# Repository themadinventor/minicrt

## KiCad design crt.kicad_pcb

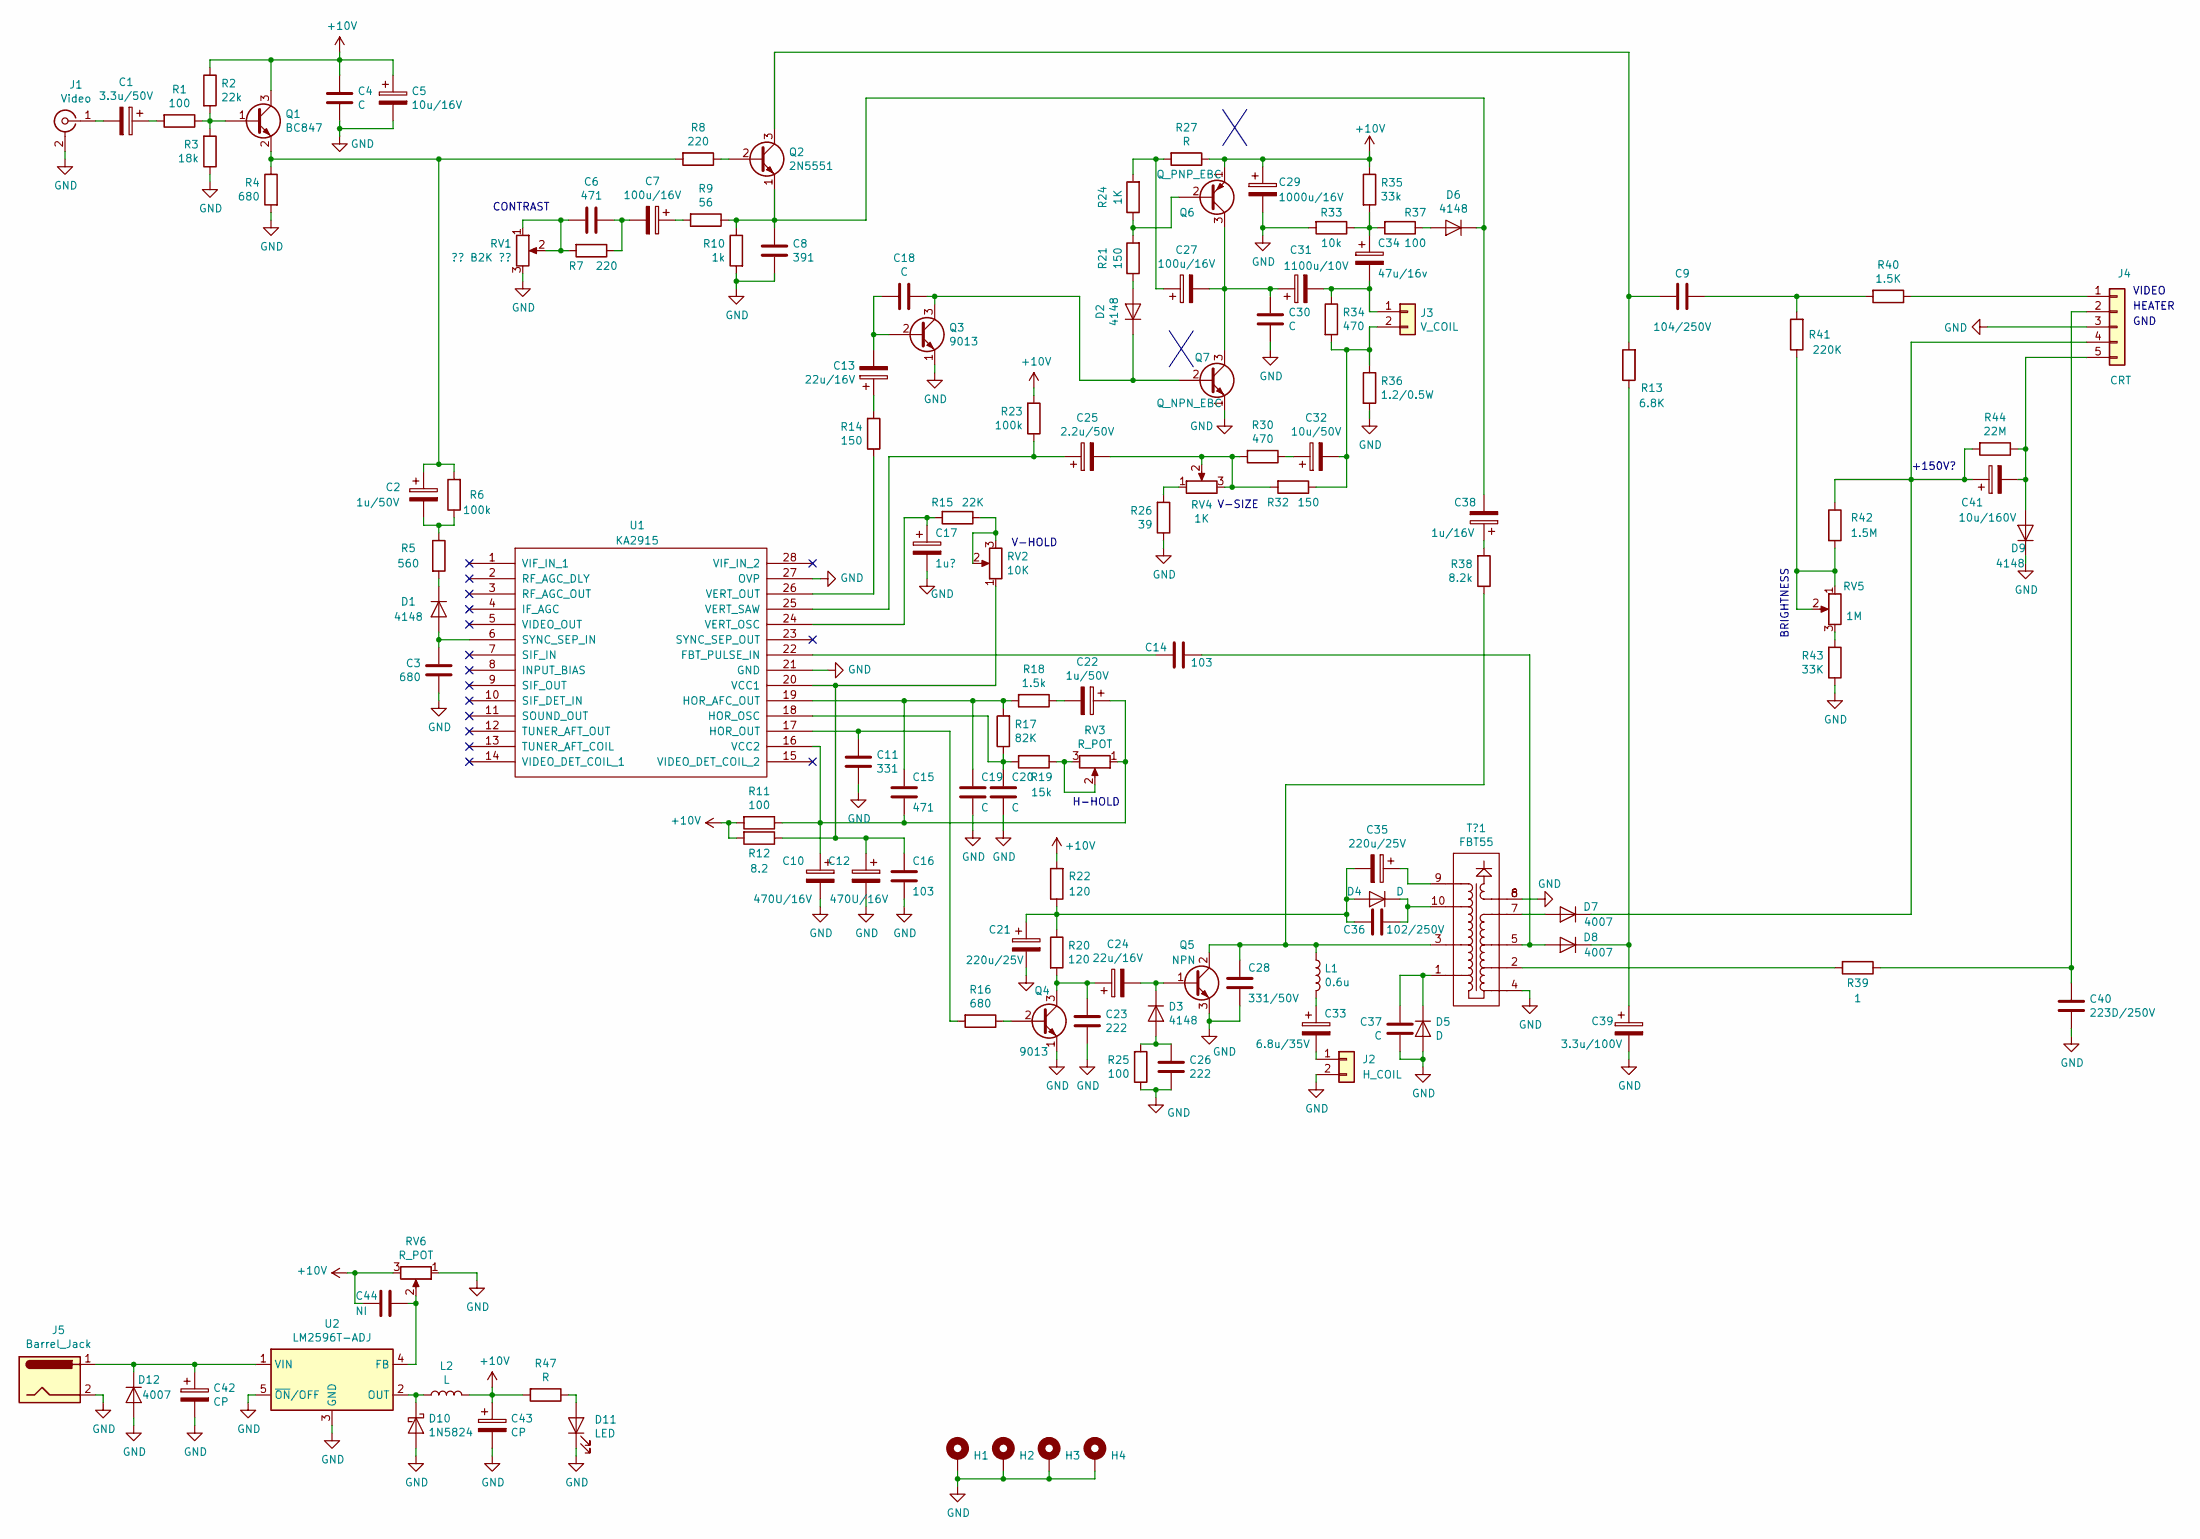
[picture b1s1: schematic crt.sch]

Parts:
C1: 3.3u/50V; CP_Radial_D5.0mm_P2.50mm
C2, C22: 1u/50V; CP_Radial_D5.0mm_P2.50mm
C3: 680; C_Disc_D5.0mm_W2.5mm_P2.50mm
C4, C18, C19, C20, C30, C37: C; C_Disc_D5.0mm_W2.5mm_P2.50mm
C5: 10u/16V; CP_Radial_D5.0mm_P2.50mm
C6, C15: 471; C_Disc_D5.0mm_W2.5mm_P2.50mm
C7: 100u/16V; CP_Radial_D6.3mm_P2.50mm
C8: 391; C_Disc_D5.0mm_W2.5mm_P2.50mm
C9: 104/250V; C_Disc_D7.5mm_W4.4mm_P5.00mm
C10, C12: 470U/16V; CP_Radial_D5.0mm_P2.50mm
C11: 331; C_Disc_D5.0mm_W2.5mm_P2.50mm
C13, C24: 22u/16V; CP_Radial_D5.0mm_P2.50mm
C14, C16: 103; C_Disc_D5.0mm_W2.5mm_P2.50mm
C17: 1u?; CP_Radial_D5.0mm_P2.50mm
C21: 220u/25V; CP_Radial_D8.0mm_P3.50mm
C23, C26: 222; C_Disc_D5.0mm_W2.5mm_P2.50mm
C25: 2.2u/50V; CP_Radial_D5.0mm_P2.50mm
C27: 100u/16V; CP_Radial_D5.0mm_P2.50mm
C28: 331/50V; C_Disc_D5.0mm_W2.5mm_P2.50mm
C29: 1000u/16V; CP_Radial_D7.5mm_P2.50mm
C31: 1100u/10V; CP_Radial_D7.5mm_P2.50mm
C32: 10u/50V; CP_Radial_D7.5mm_P2.50mm
C33: 6.8u/35V; CP_Radial_D10.0mm_P2.50mm
C34: 47u/16v; CP_Radial_D5.0mm_P2.50mm
C35: 220u/25V; CP_Radial_D10.0mm_P2.50mm
C36: 102/250V; C_Disc_D5.0mm_W2.5mm_P2.50mm
C38: 1u/16V; CP_Radial_D5.0mm_P2.50mm
C39: 3.3u/100V; CP_Radial_D5.0mm_P2.50mm
C40: 223D/250V; C_Disc_D7.5mm_W4.4mm_P5.00mm
C41: 10u/160V; CP_Radial_D8.0mm_P3.80mm
C42: CP; CP_Radial_D7.5mm_P2.50mm
C43: CP; CP_Radial_D10.0mm_P2.50mm
C44: NI; C_Disc_D5.0mm_W2.5mm_P2.50mm
D1, D2, D3, D6, D9: 4148; D_DO-35_SOD27_P2.54mm_Vertical_AnodeUp
D4, D5: D; D_DO-41_SOD81_P3.81mm_Vertical_AnodeUp
D7, D8, D12: 4007; D_DO-41_SOD81_P2.54mm_Vertical_AnodeUp
D10: 1N5824; D_DO-41_SOD81_P2.54mm_Vertical_AnodeUp
D11: LED; LED_D3.0mm
H1, H2, H3, H4: MountingHole_Pad; MountingHole_3.2mm_M3_Pad_Via
J1: Video; CUI_RCJ-01
J2: H_COIL; PinHeader_1x02_P2.54mm_Vertical
J3: V_COIL; PinHeader_1x02_P2.54mm_Vertical
J4: CRT; PinHeader_1x05_P2.54mm_Vertical
J5: Barrel_Jack; BarrelJack_CUI_PJ-102AH_Horizontal
L1: 0.6u; PinHeader_1x02_P2.54mm_Vertical
L2: L; L_Radial_D12.0mm_P6.00mm_MuRATA_1900R
Q1: BC847; TO-92_Inline_Wide
Q2: 2N5551; TO-92_Inline_Wide
Q3, Q4: 9013; TO-92_Inline_Wide
Q5: NPN; TO-220-3_Vertical
Q6: Q_PNP_EBC; TO-92_Inline_Wide
Q7: Q_NPN_EBC; TO-92_Inline_Wide
R1, R11, R25, R37: 100; R_Axial_DIN0207_L6.3mm_D2.5mm_P10.16mm_Horizontal
R2: 22k; R_Axial_DIN0207_L6.3mm_D2.5mm_P10.16mm_Horizontal
R3: 18k; R_Axial_DIN0207_L6.3mm_D2.5mm_P10.16mm_Horizontal
R4, R16: 680; R_Axial_DIN0207_L6.3mm_D2.5mm_P10.16mm_Horizontal
R5: 560; R_Axial_DIN0207_L6.3mm_D2.5mm_P10.16mm_Horizontal
R6, R23: 100k; R_Axial_DIN0207_L6.3mm_D2.5mm_P10.16mm_Horizontal
R7, R8: 220; R_Axial_DIN0207_L6.3mm_D2.5mm_P10.16mm_Horizontal
R9: 56; R_Axial_DIN0207_L6.3mm_D2.5mm_P10.16mm_Horizontal
R10: 1k; R_Axial_DIN0207_L6.3mm_D2.5mm_P10.16mm_Horizontal
R12: 8.2; R_Axial_DIN0207_L6.3mm_D2.5mm_P10.16mm_Horizontal
R13: 6.8K; R_Axial_DIN0207_L6.3mm_D2.5mm_P10.16mm_Horizontal
R14, R21, R32: 150; R_Axial_DIN0207_L6.3mm_D2.5mm_P10.16mm_Horizontal
R15: 22K; R_Axial_DIN0207_L6.3mm_D2.5mm_P10.16mm_Horizontal
R17: 82K; R_Axial_DIN0207_L6.3mm_D2.5mm_P10.16mm_Horizontal
R18: 1.5k; R_Axial_DIN0207_L6.3mm_D2.5mm_P10.16mm_Horizontal
R19: 15k; R_Axial_DIN0207_L6.3mm_D2.5mm_P10.16mm_Horizontal
R20, R22: 120; R_Axial_DIN0207_L6.3mm_D2.5mm_P10.16mm_Horizontal
R24: 1K; R_Axial_DIN0207_L6.3mm_D2.5mm_P10.16mm_Horizontal
R26: 39; R_Axial_DIN0207_L6.3mm_D2.5mm_P10.16mm_Horizontal
R27, R47: R; R_Axial_DIN0207_L6.3mm_D2.5mm_P10.16mm_Horizontal
R30, R34: 470; R_Axial_DIN0207_L6.3mm_D2.5mm_P10.16mm_Horizontal
R33: 10k; R_Axial_DIN0207_L6.3mm_D2.5mm_P10.16mm_Horizontal
R35: 33k; R_Axial_DIN0207_L6.3mm_D2.5mm_P10.16mm_Horizontal
R36: 1.2/0.5W; R_Axial_DIN0207_L6.3mm_D2.5mm_P10.16mm_Horizontal
R38: 8.2k; R_Axial_DIN0207_L6.3mm_D2.5mm_P10.16mm_Horizontal
R39: 1; R_Axial_DIN0207_L6.3mm_D2.5mm_P10.16mm_Horizontal
R40: 1.5K; R_Axial_DIN0207_L6.3mm_D2.5mm_P10.16mm_Horizontal
R41: 220K; R_Axial_DIN0207_L6.3mm_D2.5mm_P10.16mm_Horizontal
R42: 1.5M; R_Axial_DIN0207_L6.3mm_D2.5mm_P10.16mm_Horizontal
R43: 33K; R_Axial_DIN0207_L6.3mm_D2.5mm_P10.16mm_Horizontal
R44: 22M; R_Axial_DIN0207_L6.3mm_D2.5mm_P10.16mm_Horizontal
RV1: ?? B2K ??; Potentiometer_Vishay_T73YP_Vertical
RV2: 10K; Potentiometer_Vishay_T73YP_Vertical
RV3, RV6: R_POT; Potentiometer_Vishay_T73YP_Vertical
RV4: 1K; Potentiometer_Vishay_T73YP_Vertical
RV5: 1M; Potentiometer_Vishay_T73YP_Vertical
T?1: FBT55
U1: KA2915; DIP-28_W15.24mm
U2: LM2596T-ADJ; TO-220-5_P3.4x3.7mm_StaggerOdd_Lead3.8mm_Vertical

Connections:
+10V: C4.1, C5.1, C29.1, C43.1, C44.2, L2.2, Q1.3 (C), Q6.1 (E), R2.1, R11.2, R12.2, R22.2, R23.2, R27.1, R35.1, R47.2, RV6.3
GND: C3.1, C4.2, C5.2, C8.2, C10.2, C11.2, C12.2, C16.2, C17.2, C19.2, C20.2, C21.2, C23.2, C26.2, C28.2, C29.2, C30.2, C37.1, C39.2, C40.2, C42.2, C43.2, D5.2 (A), D9.1 (K), D10.2 (A), D11.1 (K), D12.2 (A), H1.1, H2.1, H3.1, H4.1, J1.2 (Ext), J2.2, J4.3, J5.2, Q3.1 (E), Q4.1 (E), Q5.3 (E), Q7.1 (E), R3.1, R4.2, R10.2, R25.1, R26.1, R33.2, R36.2, R43.1, RV1.3, RV6.1, T?1.4, T?1.6, T?1.8, U1.21 (GND), U1.27 (OVP), U2.3 (GND), U2.5 (~ON~/OFF)
unnamed: C1.1, R1.2
unnamed: C1.2, J1.1 (In)
unnamed: C2.1, Q1.2 (E), R4.1, R6.2, R8.2
unnamed: C2.2, R5.1, R6.1
unnamed: C3.2, D1.2 (A), U1.6 (SYNC_SEP_IN)
unnamed: C6.1, C7.2, R7.1
unnamed: C6.2, R7.2, RV1.1, RV1.2
unnamed: C7.1, R9.2
unnamed: C9.1, Q2.3 (C), R13.2
unnamed: C9.2, R40.2, R41.2
unnamed: C10.1, C15.2, C22.1, R11.1, RV3.1, U1.16 (VCC2)
unnamed: C11.1, R16.2, U1.17 (HOR_OUT)
unnamed: C12.1, C16.1, R12.1, RV2.1, U1.20 (VCC1)
unnamed: C13.1, R14.2
unnamed: C13.2, C18.2, Q3.2 (B)
unnamed: C14.1, D8.2 (A), T?1.5
unnamed: C14.2, U1.22 (FBT_PULSE_IN)
unnamed: C15.1, C19.1, R17.2, R18.2, U1.19 (HOR_AFC_OUT)
unnamed: C17.1, R15.2, U1.24 (VERT_OSC)
unnamed: C18.1, D2.1 (K), Q3.3 (C), Q7.2 (B)
unnamed: C20.1, R17.1, R19.2, U1.18 (HOR_OSC)
unnamed: C21.1, C35.2, C36.2, D4.2 (A), R20.1, R22.1
unnamed: C22.2, R18.1
unnamed: C23.1, C24.1, Q4.3 (C), R20.2
unnamed: C24.2, D3.1 (K), Q5.1 (B)
unnamed: C25.1, R23.1, U1.25 (VERT_SAW)
unnamed: C25.2, R30.2, R32.2, RV4.2, RV4.3
unnamed: C26.1, D3.2 (A), R25.2
unnamed: C27.1, R24.2, R27.2
unnamed: C27.2, C30.1, C31.1, Q6.3 (C), Q7.3 (C)
unnamed: C28.1, L1.1, Q5.2 (C), R38.1, T?1.3
unnamed: C31.2, C34.2, J3.1, R34.1
unnamed: C32.1, R30.1
unnamed: C32.2, J3.2, R32.1, R34.2, R36.1
unnamed: C33.1, L1.2
unnamed: C33.2, J2.1
unnamed: C34.1, R33.1, R35.2, R37.2
unnamed: C35.1, T?1.9
unnamed: C36.1, D4.1 (K), T?1.10
unnamed: C37.2, D5.1 (K), T?1.1
unnamed: C38.1, R38.2
unnamed: C8.1, C38.2, D6.1 (K), Q2.1 (E), R9.1, R10.1
unnamed: C39.1, D8.1 (K), R13.1
unnamed: C40.1, J4.2, R39.1
unnamed: C41.1, D7.1 (K), J4.4, R42.1, R44.2
unnamed: C41.2, D9.2 (A), J4.5, R44.1
unnamed: C42.1, D12.1 (K), J5.1, U2.1 (VIN)
unnamed: C44.1, RV6.2, U2.4 (FB)
unnamed: D1.1 (K), R5.2
unnamed: D2.2 (A), R21.1
unnamed: D6.2 (A), R37.1
unnamed: D7.2 (A), T?1.7
unnamed: D10.1 (K), L2.1, U2.2 (OUT)
unnamed: D11.2 (A), R47.1
unnamed: J4.1, R40.1
unnamed: Q1.1 (B), R1.1, R2.2, R3.2
unnamed: Q2.2 (B), R8.1
unnamed: Q4.2 (B), R16.1
unnamed: Q6.2 (B), R21.2, R24.1
unnamed: R14.1, U1.26 (VERT_OUT)
unnamed: R15.1, RV2.2, RV2.3
unnamed: R19.1, RV3.2, RV3.3
unnamed: R26.2, RV4.1
unnamed: R39.2, T?1.2
unnamed: R41.1, R42.2, RV5.1, RV5.2
unnamed: R43.2, RV5.3

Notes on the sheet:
V-HOLD
H-HOLD
CONTRAST
V-SIZE
BRIGHTNESS
+150V?
HEATER
VIDEO
GND

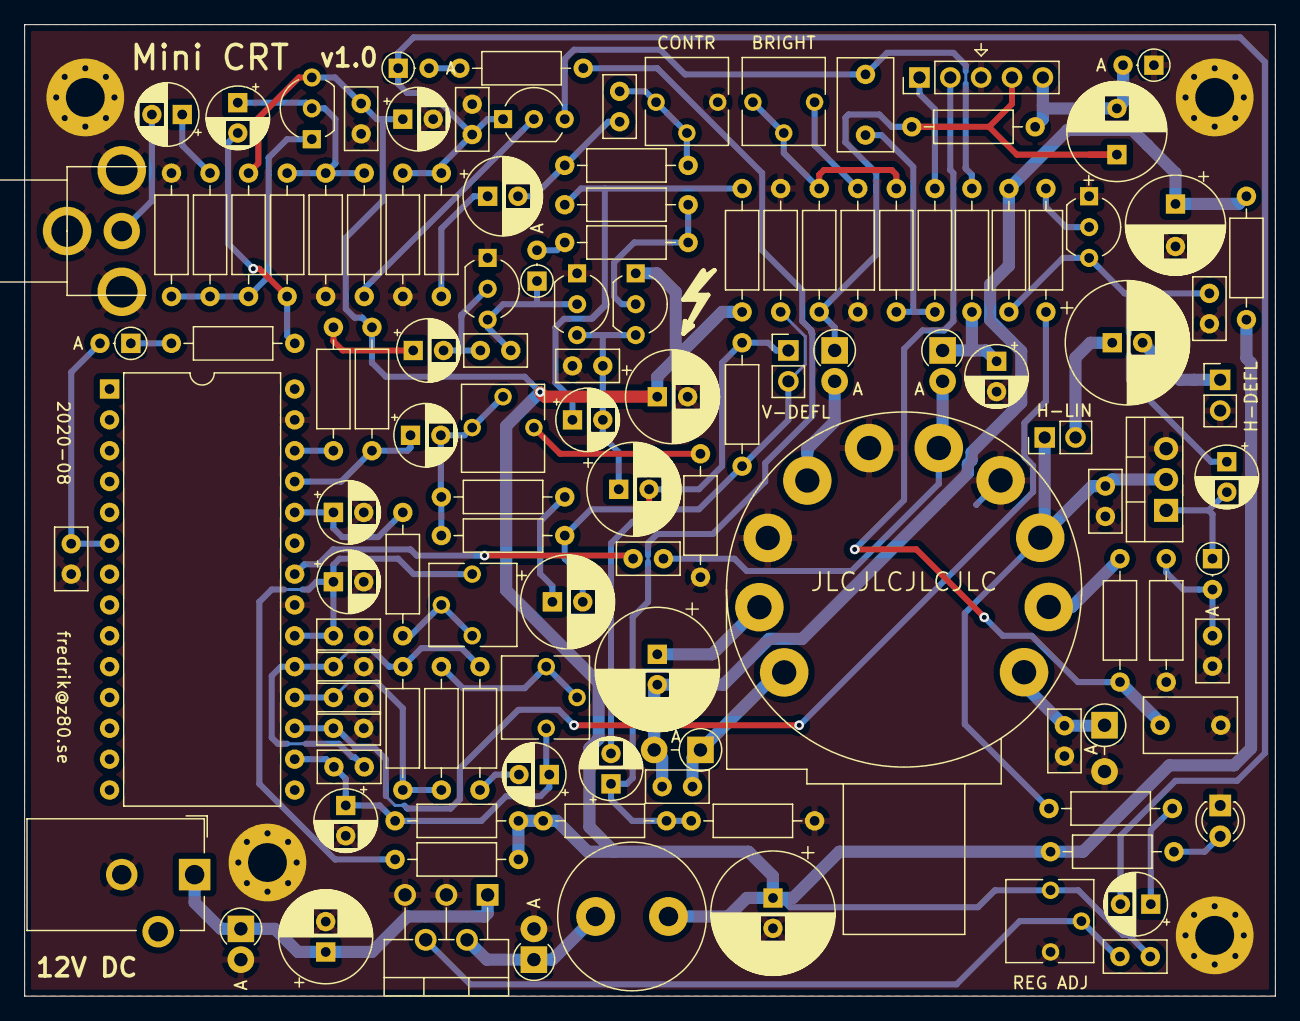
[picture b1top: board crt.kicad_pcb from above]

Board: 2 copper layers, 103.0 x 80.0 mm, 125 parts (0 on the bottom side), 68 nets.

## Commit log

2020-08-16 import
2020-08-16 add doc
2020-08-16 fix munting pads, camera ready?
